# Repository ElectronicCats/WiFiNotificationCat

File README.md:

# NotificationCat

Electronic Cats invests time and resources providing this open source design, please support Electronic Cats and open-source hardware by purchasing products from Electronic Cats!

Designed by Electronic Cats.

Firmware released under an GNU AGPL v3.0 license. See the LICENSE file for more information.

Hardware released under an CERN Open Hardware Licence v1.2. See the LICENSE_HARDWARE file for more information.

Electronic Cats is a registered trademark, please do not use if you sell these PCBs.

12 Dec 2017

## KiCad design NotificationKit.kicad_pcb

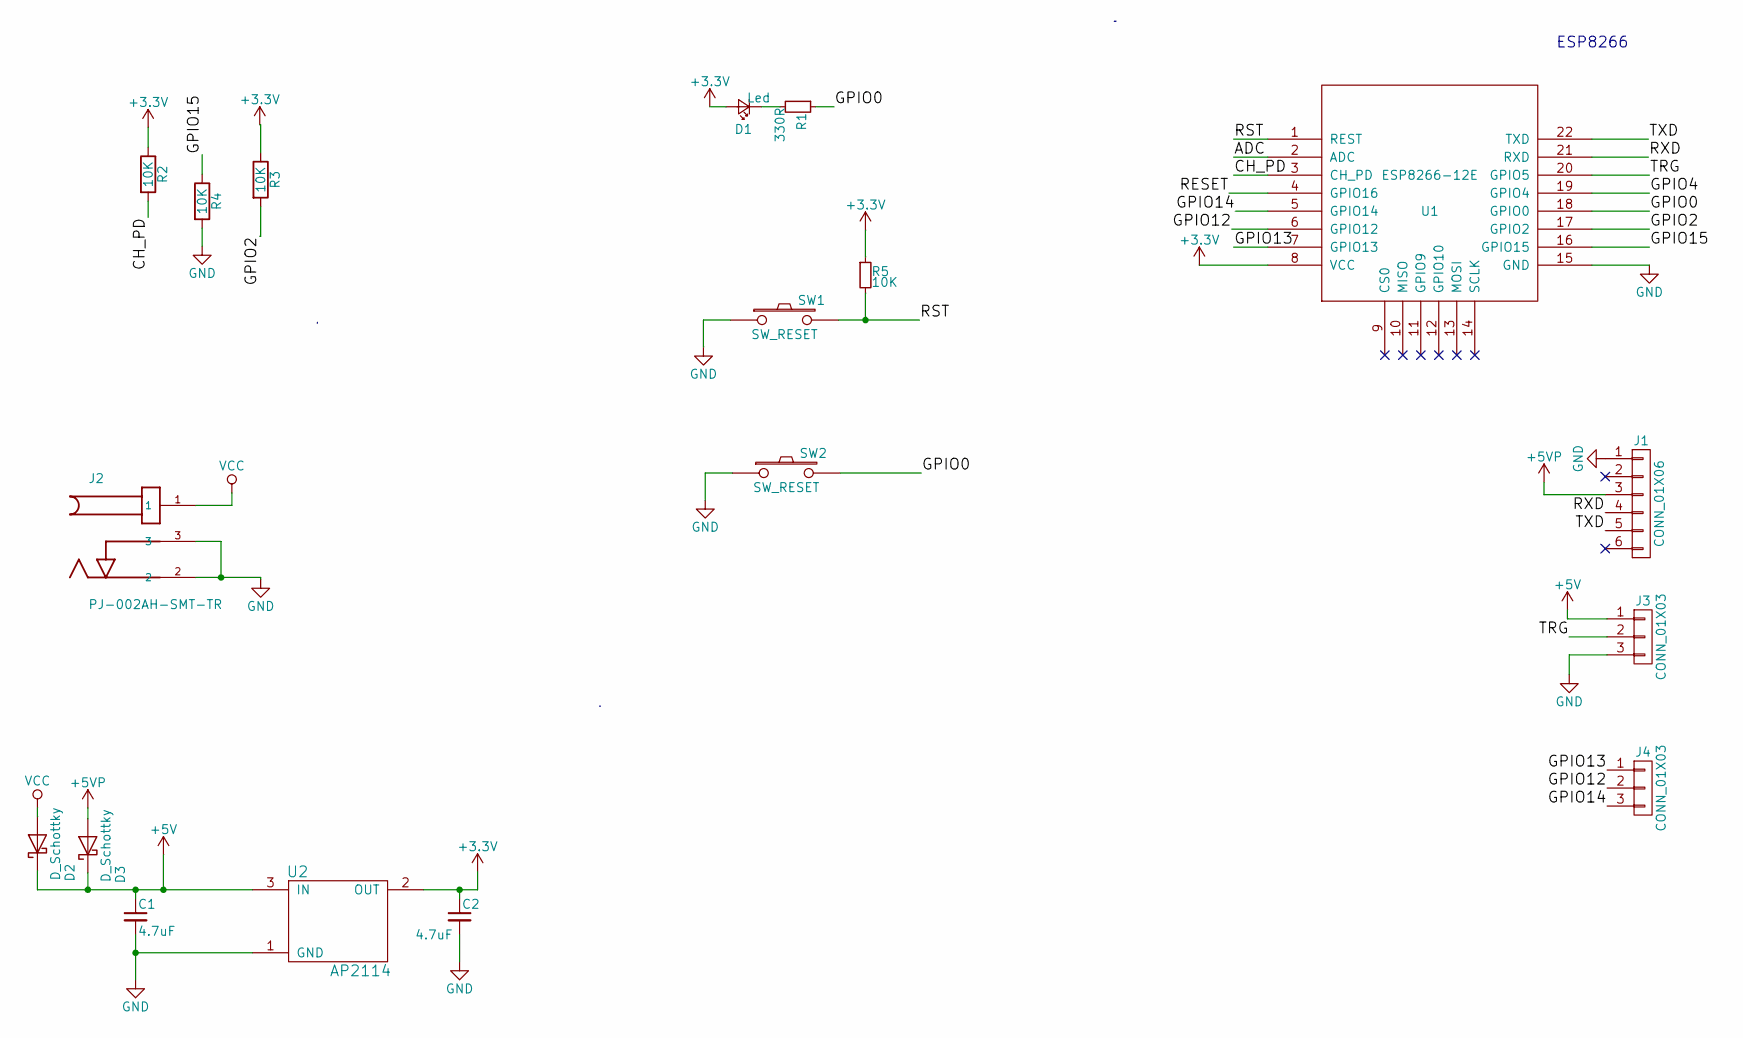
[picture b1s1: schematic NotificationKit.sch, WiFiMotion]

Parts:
C1, C2: 4.7uF; C_0805_HandSoldering
D1: Led; LED_0805
D2, D3: D_Schottky; D_SOD-123
J1: CONN_01X06; Pin_Header_Straight_1x06_Pitch2.54mm
J2: PJ-002AH-SMT-TR; CUI-PJ-002AH-SMT_dc-barrel-jack
J3, J4: CONN_01X03; Pin_Header_Straight_1x03_Pitch2.54mm
R1: 330R; R_0805_HandSoldering
R2, R3, R4, R5: 10K; R_0805_HandSoldering
SW1, SW2: SW_RESET; SW_SPST_B3U-1000P
U1: ESP8266-12E; ESP-12E
U2: AP2114; SOT-223-3_TabPin2

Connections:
+3V3: C2.1, D1.2 (A), R2.1, R3.1, R5.1, U1.8 (VCC), U2.2 (OUT)
+5V: C1.1, D2.1 (K), D3.1 (K), J3.1, U2.3 (IN)
+5VP: D3.2 (A), J1.3
/ADC: U1.2 (ADC)
/CH_PD: R2.2, U1.3 (CH_PD)
/GPIO0: R1.1, SW2.2, U1.18 (GPIO0)
/GPIO2: R3.2, U1.17 (GPIO2)
/GPIO4: U1.19 (GPIO4)
/GPIO12: J4.2, U1.6 (GPIO12)
/GPIO13: J4.1, U1.7 (GPIO13)
/GPIO14: J4.3, U1.5 (GPIO14)
/GPIO15: R4.1, U1.16 (GPIO15)
/RESET: U1.4 (GPIO16)
/RST: R5.2, SW1.2, U1.1 (REST)
/RXD: J1.4, U1.21 (RXD)
/TRG: J3.2, U1.20 (GPIO5)
/TXD: J1.5, U1.22 (TXD)
GND: C1.2, C2.2, J1.1, J2.2, J2.3, J3.3, R4.2, SW1.1, SW2.1, U1.15 (GND), U2.1 (GND)
unnamed: D1.1 (K), R1.2
VCC: D2.2 (A), J2.1

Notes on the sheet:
ESP8266

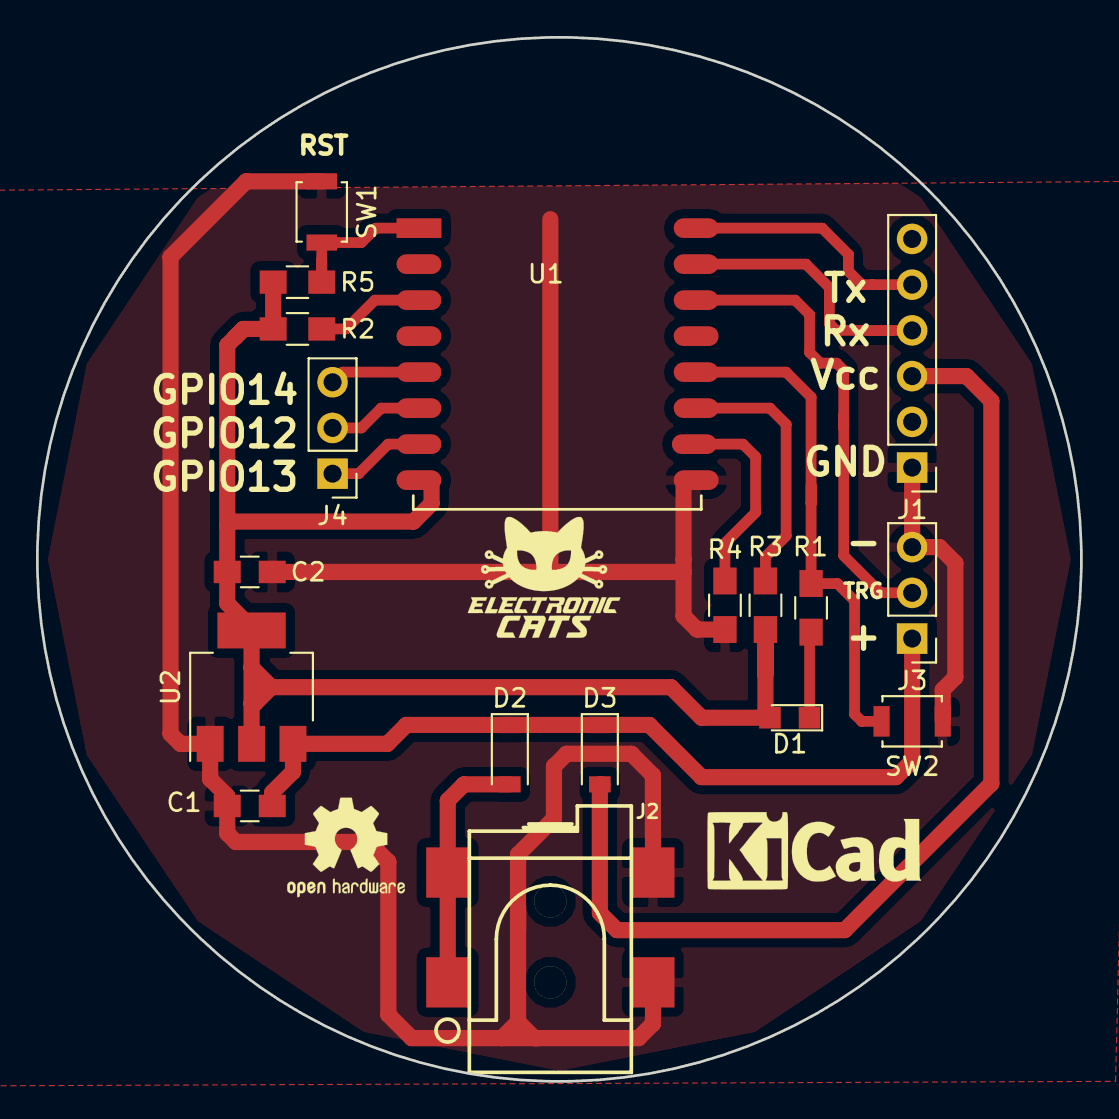
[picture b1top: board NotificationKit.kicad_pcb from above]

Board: 2 copper layers, 58.0 x 58.0 mm, 18 parts (0 on the bottom side), 17 nets.

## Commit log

2017-12-12 Add Schematic
2017-12-12 Add library
2017-12-12 Add gitignore
2018-01-19 Added logo EC
2018-01-19 Config gerbers
